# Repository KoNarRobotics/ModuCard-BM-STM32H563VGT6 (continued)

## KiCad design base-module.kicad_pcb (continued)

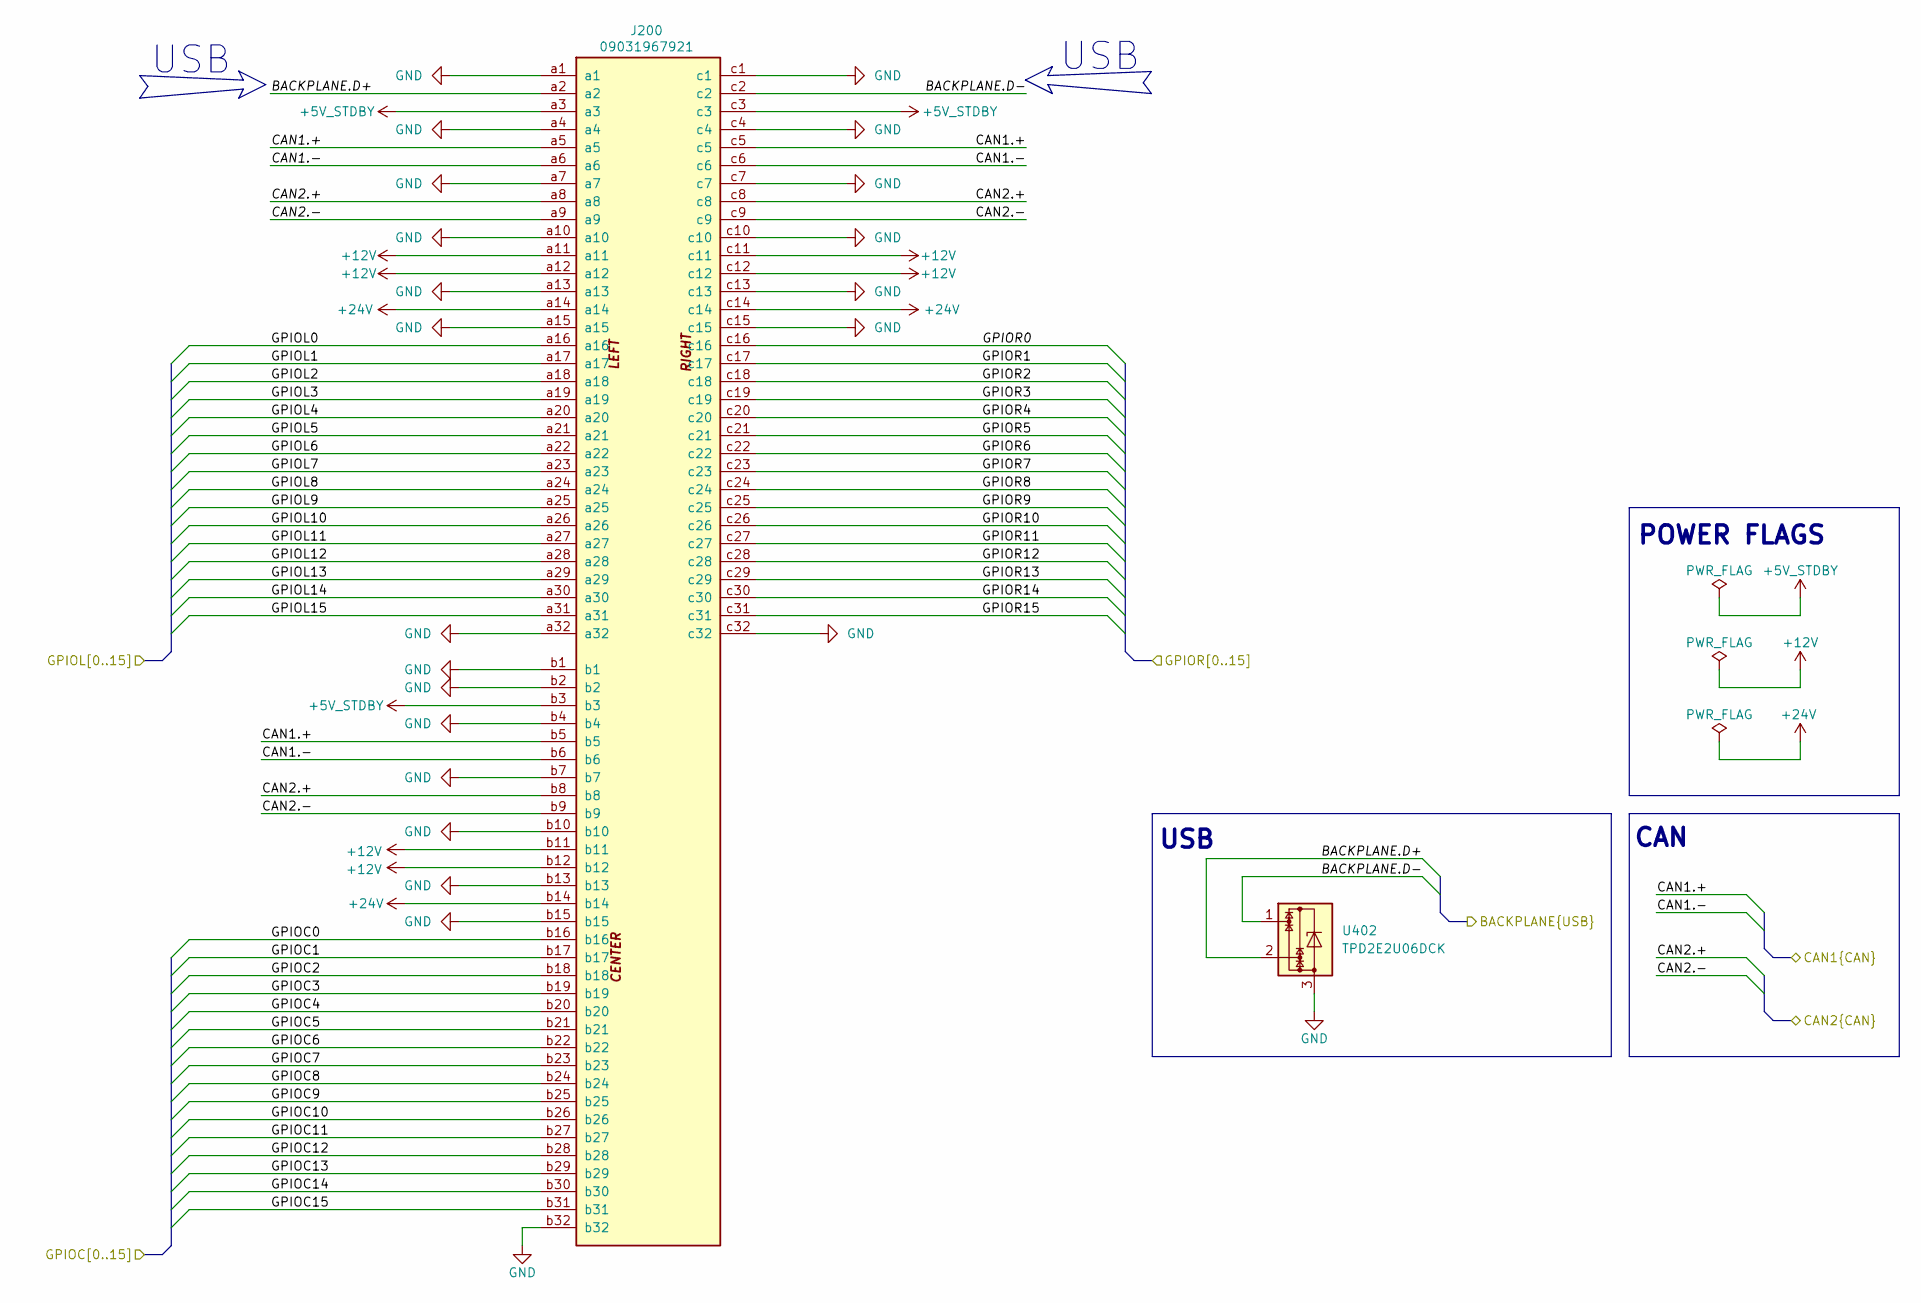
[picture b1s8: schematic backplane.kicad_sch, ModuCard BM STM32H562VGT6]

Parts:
J200: 09031967921; DIN41612_R_3x32_Female_Horizontal_THT; PARTREV D
U402: TPD2E2U06DCK; SOT-323_SC-70

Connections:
+5V_STDBY: J200.a3, J200.b3, J200.c3
+12V: J200.a11, J200.a12, J200.b11, J200.b12, J200.c11, J200.c12; also elsewhere on the board
+24V: J200.a14, J200.b14, J200.c14
/Backplane/BACKPLANE.D+: J200.a2, U402.2; also elsewhere on the board
/Backplane/BACKPLANE.D-: J200.c2, U402.1; also elsewhere on the board
/Backplane/CAN1.+: J200.a5, J200.b5, J200.c5; also elsewhere on the board
/Backplane/CAN1.-: J200.a6, J200.b6, J200.c6; also elsewhere on the board
/Backplane/CAN2.+: J200.a8, J200.b8, J200.c8; also elsewhere on the board
/Backplane/CAN2.-: J200.a9, J200.b9, J200.c9; also elsewhere on the board
/Backplane/GPIOC0: J200.b16
/Backplane/GPIOC1: J200.b17
/Backplane/GPIOC2: J200.b18
/Backplane/GPIOC3: J200.b19
/Backplane/GPIOC4: J200.b20
/Backplane/GPIOC5: J200.b21
/Backplane/GPIOC6: J200.b22
/Backplane/GPIOC7: J200.b23
/Backplane/GPIOC8: J200.b24
/Backplane/GPIOC9: J200.b25
/Backplane/GPIOC10: J200.b26
/Backplane/GPIOC11: J200.b27
/Backplane/GPIOC12: J200.b28
/Backplane/GPIOC13: J200.b29
/Backplane/GPIOC14: J200.b30
/Backplane/GPIOC15: J200.b31
/Backplane/GPIOL0: J200.a16
/Backplane/GPIOL1: J200.a17
/Backplane/GPIOL2: J200.a18
/Backplane/GPIOL3: J200.a19
/Backplane/GPIOL4: J200.a20
/Backplane/GPIOL5: J200.a21
/Backplane/GPIOL6: J200.a22
/Backplane/GPIOL7: J200.a23
/Backplane/GPIOL8: J200.a24
/Backplane/GPIOL9: J200.a25
/Backplane/GPIOL10: J200.a26
/Backplane/GPIOL11: J200.a27
/Backplane/GPIOL12: J200.a28
/Backplane/GPIOL13: J200.a29
/Backplane/GPIOL14: J200.a30
/Backplane/GPIOL15: J200.a31
/Backplane/GPIOR0: J200.c16
/Backplane/GPIOR1: J200.c17
/Backplane/GPIOR2: J200.c18
/Backplane/GPIOR3: J200.c19
/Backplane/GPIOR4: J200.c20
/Backplane/GPIOR5: J200.c21
/Backplane/GPIOR6: J200.c22
/Backplane/GPIOR7: J200.c23
/Backplane/GPIOR8: J200.c24
/Backplane/GPIOR9: J200.c25
/Backplane/GPIOR10: J200.c26
/Backplane/GPIOR11: J200.c27
/Backplane/GPIOR12: J200.c28
/Backplane/GPIOR13: J200.c29
/Backplane/GPIOR14: J200.c30
/Backplane/GPIOR15: J200.c31
GND: J200.a1, J200.a4, J200.a7, J200.a10, J200.a13, J200.a15, J200.a32, J200.b1, J200.b2, J200.b4, J200.b7, J200.b10, J200.b13, J200.b15, J200.b32, J200.c1, J200.c4, J200.c7, J200.c10, J200.c13, J200.c15, J200.c32, U402.3; also elsewhere on the board

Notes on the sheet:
USB
CAN
POWER FLAGS
USB

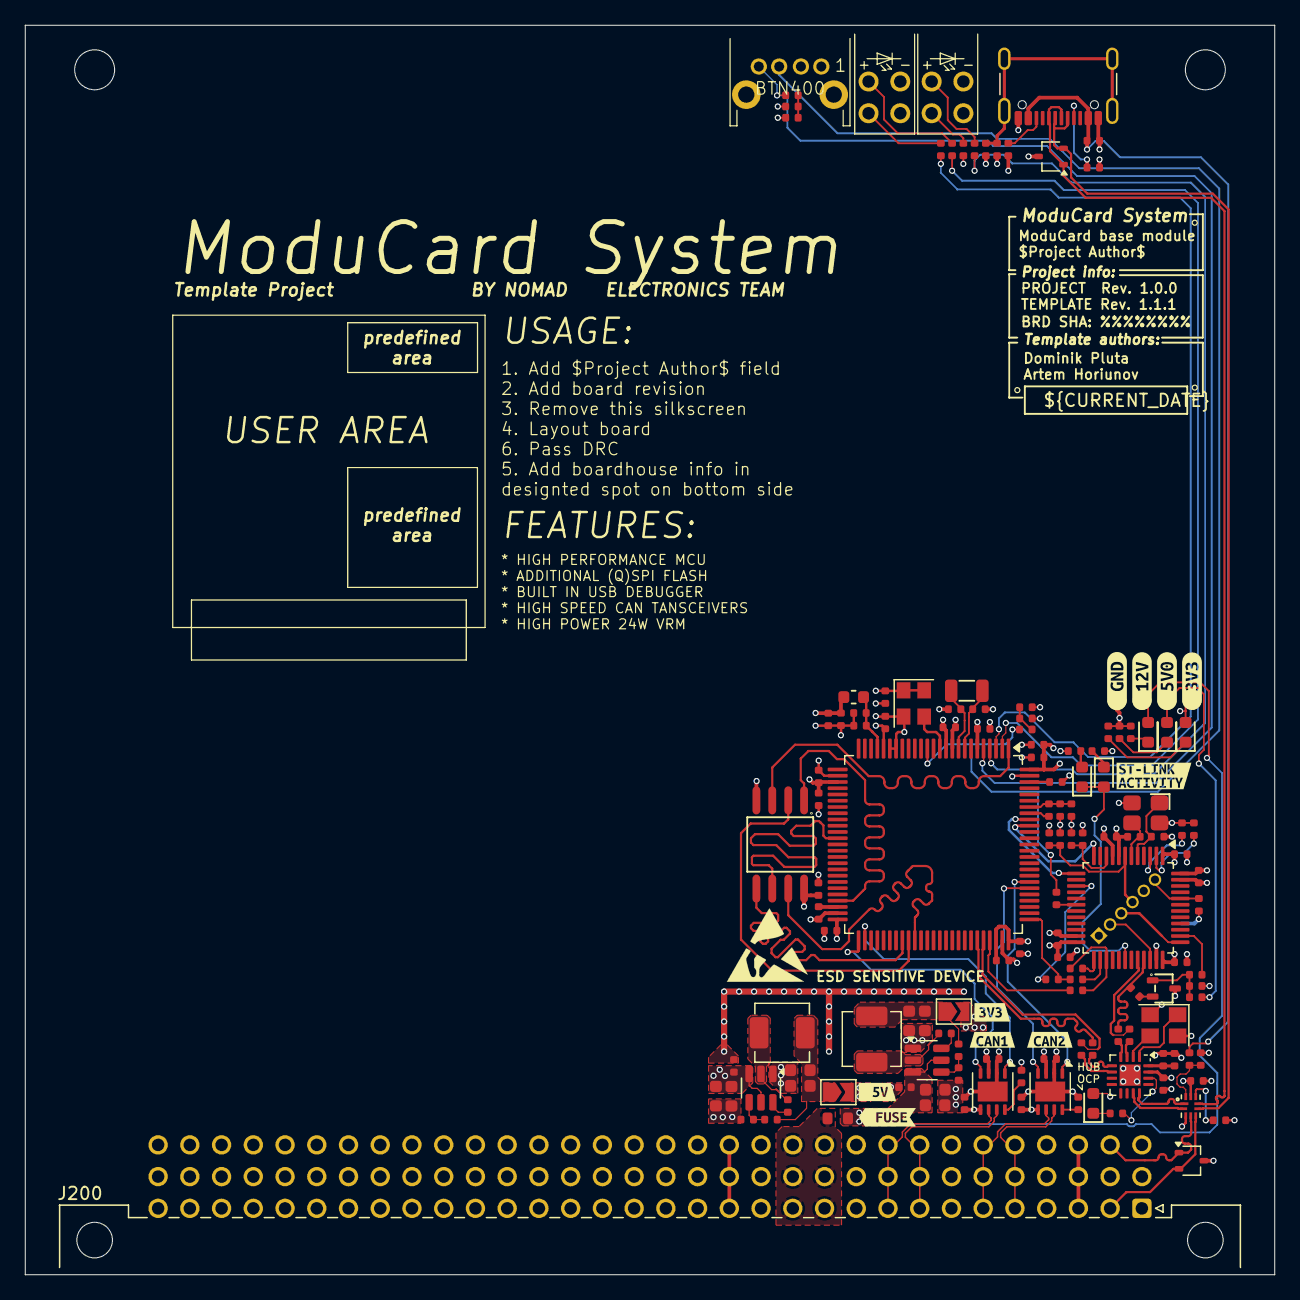
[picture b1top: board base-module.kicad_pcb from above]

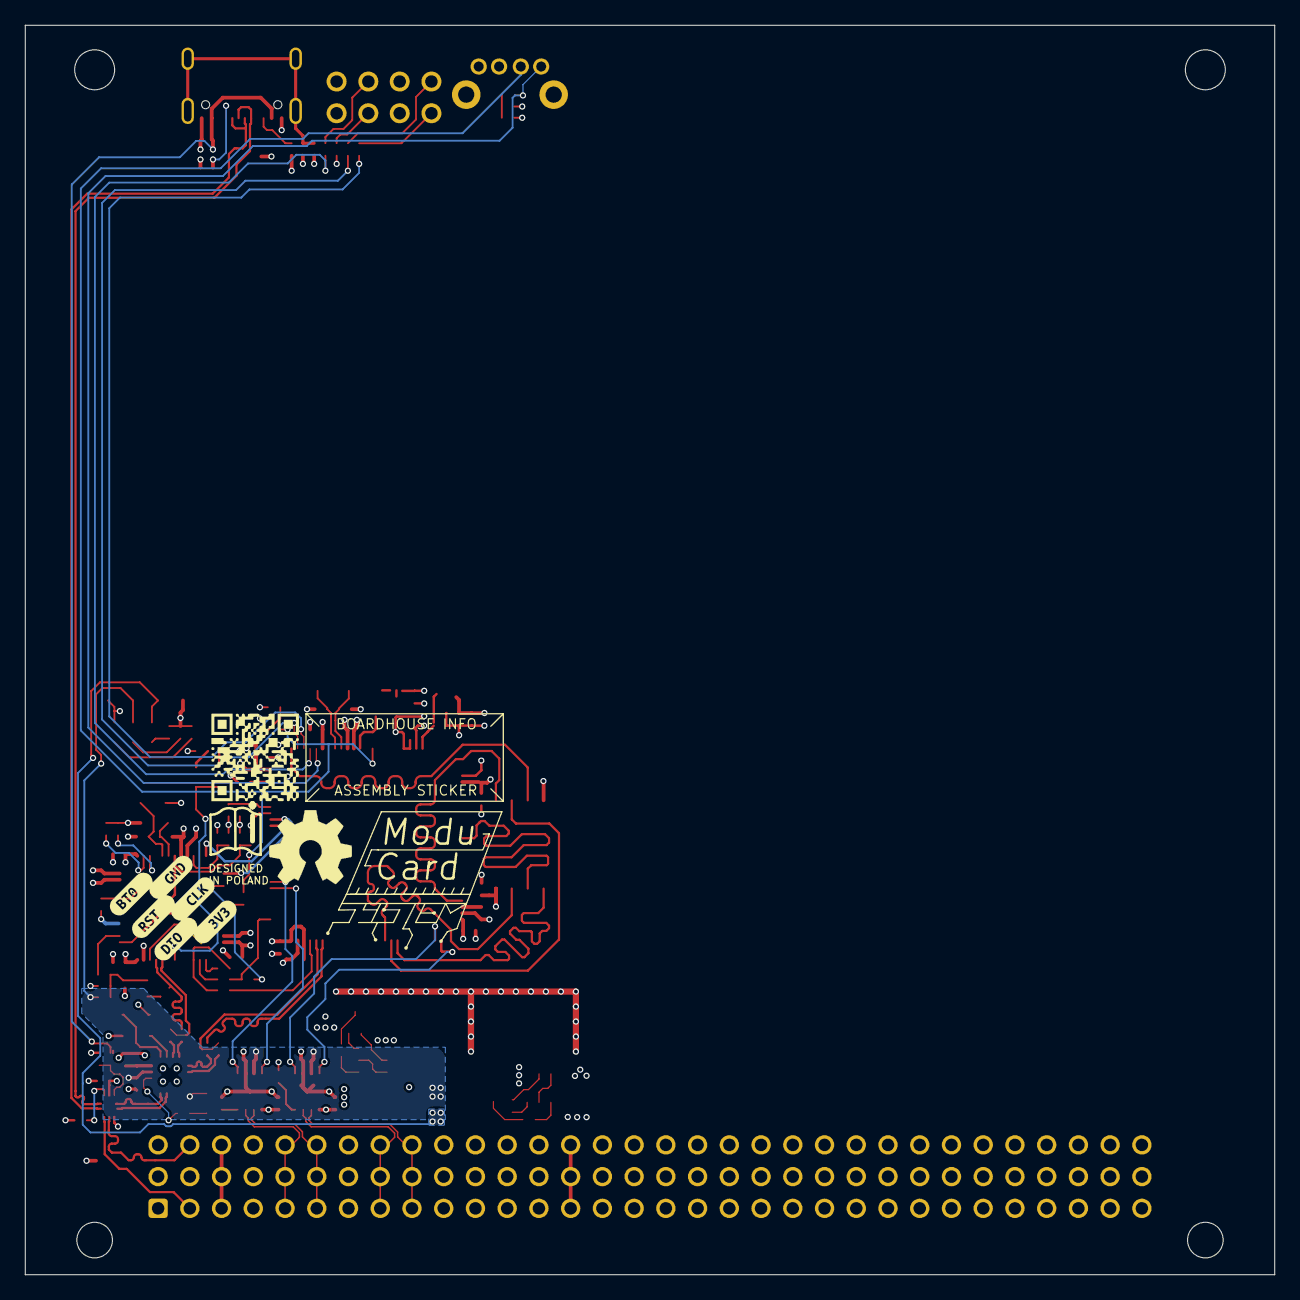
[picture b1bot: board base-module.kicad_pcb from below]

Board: 4 copper layers, 100.0 x 100.0 mm, 155 parts (7 on the bottom side), 102 nets.

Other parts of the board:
kibuzzard-67B20BD5: G***; kibuzzard-67B20BD5
kibuzzard-67B63E8D: G***; kibuzzard-67B63E8D
kibuzzard-67B643AC: G***; kibuzzard-67B643AC
kibuzzard-67B643DE: G***; kibuzzard-67B643DE
kibuzzard-67B643EE: G***; kibuzzard-67B643EE
kibuzzard-67B6249A: G***; kibuzzard-67B6249A
kibuzzard-67B6438D: G***; kibuzzard-67B6438D
kibuzzard-67B37005: G***; kibuzzard-67B37005
kibuzzard-67B37418: G***; kibuzzard-67B37418
kibuzzard-67B37472: G***; kibuzzard-67B37472
kibuzzard-67B62451: G***; kibuzzard-67B62451
kibuzzard-67E7D86B: G***; kibuzzard-67E7D86B
kibuzzard-68DC416C: G***; kibuzzard-68DC416C
kibuzzard-68DC4137: G***; kibuzzard-68DC4137
kibuzzard-68DC4152: G***; kibuzzard-68DC4152
kibuzzard-68DC4179: G***; kibuzzard-68DC4179

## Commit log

2025-05-28 [#8] Bump project to rev.1.1.1
2025-06-19 [#8] Fix LEDs resistors values
2025-09-30 changed stm to stm32H564VGT, added uart for debug to stlink and new programing adapter was added
2025-09-30 Add generated schematic PDF and Gerber files
